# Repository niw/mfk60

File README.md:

mfk60
=====

60% ANSI Layout Split Keyboard. mfk60 is My First Keyboard, 60%.

- A split keyboard that has 60% ANSI Layout.
- Swappable Gateron Low-Profile MX keycap compatible switches.
- Thin design as MacBook Pro.
- USB-C interface.
- Fully customizable with [QMK firmware](https://qmk.fm/) and
  [VIA](https://www.caniusevia.com/) configuration.

Overview
--------

mfk60 is built with 4 layered boards, the top plate, middle plate, primary
PCB where the entire circuit exists, and bottom plate.

Each board is designed in separated KiCad project due to limitation of
KiCad which project can have only one board design.
Each layer board design contains both left and right designs.

- `sym-lib-table`, `fp-lib-table` are shared for additional symbol and
  footprint for all PCBs.
- `Library` contains additional symbols and footprints to KiCad.
- `mfk60.kicad_*` is the primary PCB of the keyboard.
- `mfk60_*_plate.kicad_*` are the each board layered with
  the primary PCB.
- `bin` contains tooling scripts.
- `mfk60_keyboard-layout.json` is key layout file for
  [Keyboard Layout Editor](http://www.keyboard-layout-editor.com/).

Photos
------

Build
-----

Since mfk60 is built with multiple KiCad projects, there are tooling
scripts to make the process easier.

### Overview

- `mfk60_keyboard-layout.json` to set the key layout.
- `make apply_layout` to apply the key layout to the primary PCB.
- `bin/prepare_plate_board.py` to sync the primary PCB and
  other layered board.
- `make panelize` to produce panelized boards that has frame and
  mouse bites.
- Produce Gerber files and BOM manually from KiCad projects for each board.

### Prerequisite

The board and tooling scripts are implemented by using
[KiCad](https://www.kicad.org/) 7.0.10 on macOS.

Please use KiCad 7.0.10 (or later, which is not tested.)

It should work on the other platform, however, you may need to use
`KICAD_PYTHON_PATH` to set where KiCad `python` exists
if it's not macOS or KiCad is installed on the different path
as like following.

```bash
env KICAD_PYTHON_PATH=/path/to/kicad/python bin/python.sh bin/update_plate_board.py
```

Each board is using symbols and footprints served from
[KiKit](https://github.com/yaqwsx/KiKit), which is referenced from
`.venv` library installation.
Thus, to open these PCB files, first need to install KiKit library.
To install KiKit, simply run `bin/kikit.sh`.

### Set key layout

Edit key layout on [Keyboard Layout Editor](http://www.keyboard-layout-editor.com/),
export the layout to `mfk60_keyboard-layout.json` then
use `apply_layout` goal to sync `mfk60_keyboard-layout.json`
to the primary PCB.

```bash
make apply_layout
```

Of course, it will invalidate existing PCB design, thus changing key
layout causes A LOT of work downstream.

### Sync layered boards

To sync Edge Cut and footprint positioning between the primary PCB and
the layered boards, use `bin/update_plate_board.py` with `bin/python.sh`.

```bash
bin/python.sh bin/update_plate_board.py
```

### Add frame and panelize

To produce final panelized projects with frame, use `panelize` make goal.

```bash
make panelize
```

This goal produces `mfk60*_panelized.kicad_*` files.
It adds frame, mouse bites and moves `JLCJLCJLCJLC` text onto the frame,
where is replaced with order number by [JLCPCB](https://jlcpcb.com/).

Panelized projects are final data that can be used to produce production
Gerber data. Recommend to use
[Fabrication Toolkit](https://github.com/bennymeg/JLC-Plugin-for-KiCad)
for JLCPCB but not limited ot it.

KiKit
-----

Due to multiple reasons as described below, this project is using
[forked version of KiKit](https://github.com/niw/KiKit/tree/v1.4.0_with_workaround).
`bin/kikit.sh` is automatically installs forked version of it in `.venv`,
therefore it's opaque to you.

### KiCad and Python Bindings

As of day this document is written, KiCad 7.0.10 and prior version has
a not well-known "behavior" (or simply say, a bug) in its Python binding
generated by [Swig](https://www.swig.org/).

Due to this issue, released KiKit will not work properly and may crash.
The forked version of it contains a workaround for this behavior.

### Multiple Polygons

Each layered board has both left and right ones, therefore each outline
is represented as multiple polygons.
However, original KiKit is not considering such multi polygon design and
failed to extract interior polygons which causes an error while
panelizing such data.

Firmware
--------

Use [forked QMK branch](https://github.com/niw/qmk_firmware/tree/mfk)
where contains the keyboard configuration.

```bash
qmk compile -kb niw/mfk60 -km default
```

It also works with VIA. Use `via` keymap and load
[`via.json`](https://github.com/niw/qmk_firmware/blob/mfk/keyboards/niw/mfk60/via.json)
for a draft definition in design tab enabled in settings.

```bash
qmk compile -kb niw/mfk60 -km via
```

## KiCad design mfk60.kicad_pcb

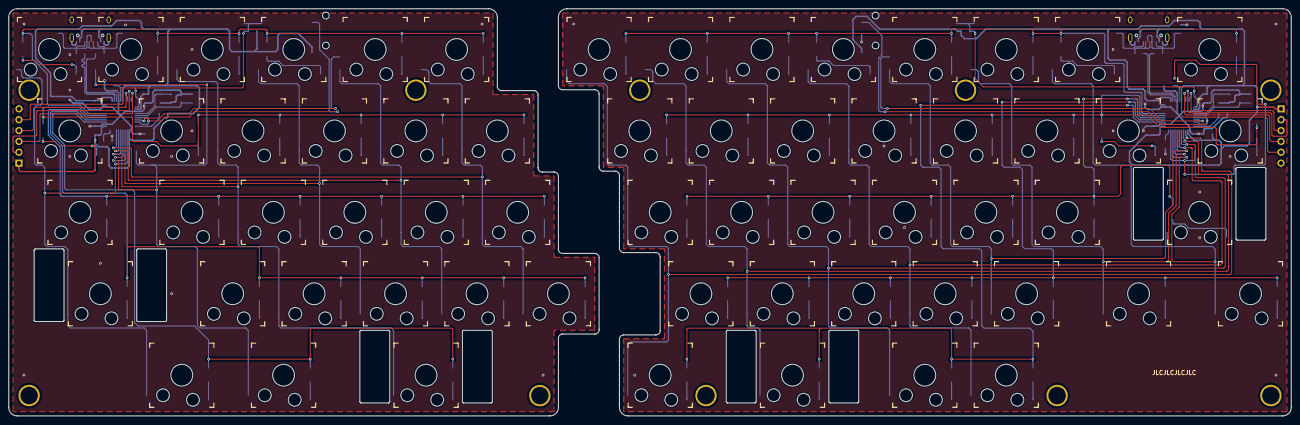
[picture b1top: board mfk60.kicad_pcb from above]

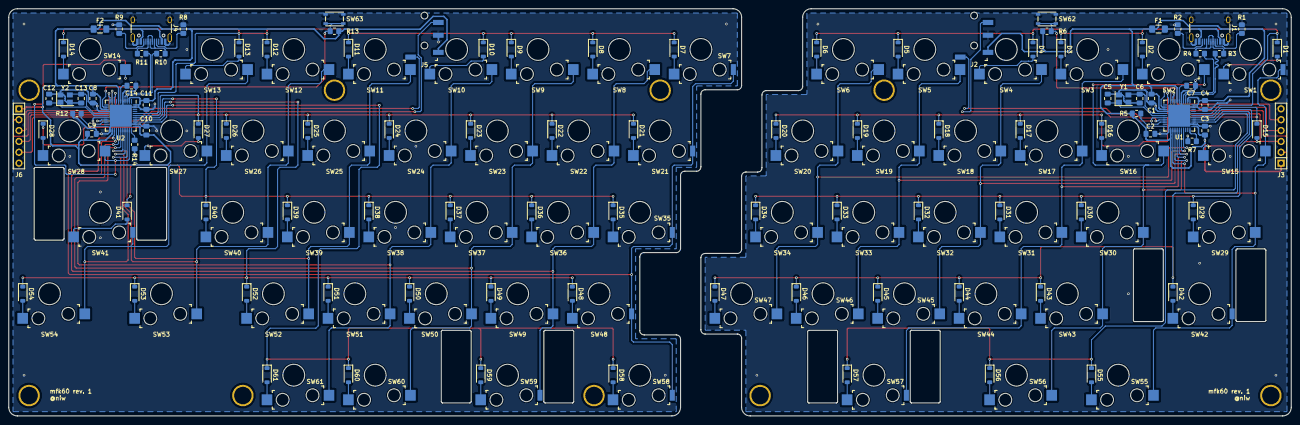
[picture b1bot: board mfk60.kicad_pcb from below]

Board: 2 copper layers, 300.0 x 95.2 mm, 181 parts (113 on the bottom side), 125 nets.

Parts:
C1, C2, C3, C8, C9, C10: 100n; C_0805_2012Metric_Pad1.18x1.45mm_HandSolder
C4, C11: 10u; C_0805_2012Metric_Pad1.18x1.45mm_HandSolder
C5, C6, C12, C13: 22p; C_0805_2012Metric_Pad1.18x1.45mm_HandSolder
C7, C14: 1u; C_0805_2012Metric_Pad1.18x1.45mm_HandSolder
D1, D2, D3, D4, D5, D6, D7, D8, D9, D10, D11, D12, D13, D14, D15, D16, D17, D18, D19, D20, D21, D22, D23, D24, D25, D26, D27, D28, D29, D30, D31, D32, D33, D34, D35, D36, D37, D38, D39, D40, D41, D42, D43, D44, D45, D46, D47, D48, D49, D50, D51, D52, D53, D54, D55, D56, D57, D58, D59, D60, D61: D; D_SOD-123
F1, F2: 500m; Fuse_1206_3216Metric_Pad1.42x1.75mm_HandSolder
H1, H2, H3, H4, H5, H6, H7, H8, H9, H10: MountingHole; MountingHole_4mm_Spacer
J1, J4: USB_C_Receptacle_USB2.0; USB_C_Receptacle_HRO_TYPE-C-31-M-12
J2, J5: TRRS Jack; TRRS_Jack_3.5mm_PJ320D
J3, J6: ISP; Debug_Pin_1x6_P2.54mm
R1, R2, R8, R9: 5.1k; R_0805_2012Metric_Pad1.20x1.40mm_HandSolder
R3, R4, R10, R11: 22; R_0805_2012Metric_Pad1.20x1.40mm_HandSolder
R5, R6, R7, R12, R13, R14: 10k; R_0805_2012Metric_Pad1.20x1.40mm_HandSolder
SW1, SW7, SW21, SW35, SW48, SW58: KS-33; Gateron_Low_Profile_Socket_Edge
SW2, SW3, SW4, SW5, SW6, SW8, SW9, SW10, SW11, SW12, SW13, SW14, SW15, SW16, SW17, SW18, SW19, SW20, SW22, SW23, SW24, SW25, SW26, SW27, SW28, SW29, SW30, SW31, SW32, SW33, SW34, SW36, SW37, SW38, SW39, SW40, SW43, SW44, SW45, SW46, SW47, SW49, SW50, SW51, SW52, SW53, SW54, SW55, SW56, SW60, SW61: KS-33; Gateron_Low_Profile_Socket
SW41, SW42, SW57, SW59: KS-33; Gateron_Low_Profile_Socket_Stabilizer_2U
SW62, SW63: RST; SW_Push_Alps_Alpine_SKRPACE010
T1, T2, T3, T4, T5, T6, T7: Tab
U1, U2: ATmega32U4-M; QFN-44-1EP_7x7mm_P0.5mm_EP5.2x5.2mm
Y1, Y2: 16M; Crystal_SMD_3225-4Pin_3.2x2.5mm

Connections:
+5V: C1.2, C2.2, C3.2, C4.2, F1.2, J2.4 (Tip), J3.1, R5.2, R6.2, U1.2 (UVCC), U1.7 (VBUS), U1.14 (VCC), U1.24 (AVCC), U1.34 (VCC), U1.44 (AVCC)
/Left/USB_CC1: J1.A5 (CC1), R1.1
/Left/USB_CC2: J1.B5 (CC2), R2.1
/Left/USB_VBUS: F1.1, J1.A4 (VBUS), J1.A9 (VBUS), J1.B4 (VBUS), J1.B9 (VBUS)
/Righ/R_USB_CC1: J4.A5 (CC1), R8.1
/Righ/R_USB_CC2: J4.B5 (CC2), R9.1
/Righ/R_USB_VBUS: F2.1, J4.A4 (VBUS), J4.A9 (VBUS), J4.B4 (VBUS), J4.B9 (VBUS)
COL1: SW1.1, SW15.1, SW29.1, SW42.1, SW55.1, U1.25 (PD4)
COL2: SW2.1, SW16.1, SW30.1, SW43.1, SW56.1, U1.26 (PD6)
COL3: SW3.1, SW17.1, SW31.1, SW44.1, SW57.1, U1.27 (PD7)
COL4: SW4.1, SW18.1, SW32.1, SW45.1, U1.28 (PB4)
COL5: SW5.1, SW19.1, SW33.1, SW46.1, U1.29 (PB5)
COL6: SW6.1, SW20.1, SW34.1, SW47.1, U1.30 (PB6)
COL7: SW7.1, SW21.1, SW35.1, SW48.1, SW58.1, U2.25 (PD4)
COL8: SW8.1, SW22.1, SW36.1, SW49.1, SW59.1, U2.26 (PD6)
COL9: SW9.1, SW23.1, SW37.1, SW50.1, SW60.1, U2.27 (PD7)
COL10: SW10.1, SW24.1, SW38.1, SW51.1, SW61.1, U2.28 (PB4)
COL11: SW11.1, SW25.1, SW39.1, SW52.1, U2.29 (PB5)
COL12: SW12.1, SW26.1, SW40.1, SW53.1, U2.30 (PB6)
COL13: SW13.1, SW27.1, SW41.1, SW54.1, U2.31 (PC6)
COL14: SW14.1, SW28.1, U2.32 (PC7)
GND: C1.1, C2.1, C3.1, C4.1, C5.2, C6.2, C7.1, J1.A1 (GND), J1.A12 (GND), J1.B1 (GND), J1.B12 (GND), J1.S1 (SHIELD), J2.3 (Ring_1), J3.6, R1.2, R2.2, R7.1, SW62.2, U1.5 (UGND), U1.15 (GND), U1.23 (GND), U1.35 (GND), U1.43 (GND), U1.45 (GND), Y1.2, Y1.4
MISO: J3.3, U1.11 (PB3)
MOSI: J3.2, U1.10 (PB2)
unnamed: D1.2 (A), SW1.2
unnamed: D2.2 (A), SW2.2
unnamed: D3.2 (A), SW3.2
unnamed: D4.2 (A), SW4.2
unnamed: D5.2 (A), SW5.2
unnamed: D6.2 (A), SW6.2
unnamed: D7.2 (A), SW7.2
unnamed: D8.2 (A), SW8.2
unnamed: D9.2 (A), SW9.2
unnamed: D10.2 (A), SW10.2
unnamed: D11.2 (A), SW11.2
unnamed: D12.2 (A), SW12.2
unnamed: D13.2 (A), SW13.2
unnamed: D14.2 (A), SW14.2
unnamed: D15.2 (A), SW15.2
unnamed: D16.2 (A), SW16.2
unnamed: D17.2 (A), SW17.2
unnamed: D18.2 (A), SW18.2
unnamed: D19.2 (A), SW19.2
unnamed: D20.2 (A), SW20.2
unnamed: D21.2 (A), SW21.2
unnamed: D22.2 (A), SW22.2
unnamed: D23.2 (A), SW23.2
unnamed: D24.2 (A), SW24.2
unnamed: D25.2 (A), SW25.2
unnamed: D26.2 (A), SW26.2
unnamed: D27.2 (A), SW27.2
unnamed: D28.2 (A), SW28.2
unnamed: D29.2 (A), SW29.2
unnamed: D30.2 (A), SW30.2
unnamed: D31.2 (A), SW31.2
unnamed: D32.2 (A), SW32.2
unnamed: D33.2 (A), SW33.2
unnamed: D34.2 (A), SW34.2
unnamed: D35.2 (A), SW35.2
unnamed: D36.2 (A), SW36.2
unnamed: D37.2 (A), SW37.2
unnamed: D38.2 (A), SW38.2
unnamed: D39.2 (A), SW39.2
unnamed: D40.2 (A), SW40.2
unnamed: D41.2 (A), SW41.2
unnamed: D42.2 (A), SW42.2
unnamed: D43.2 (A), SW43.2
unnamed: D44.2 (A), SW44.2
unnamed: D45.2 (A), SW45.2
unnamed: D46.2 (A), SW46.2
unnamed: D47.2 (A), SW47.2
unnamed: D48.2 (A), SW48.2
unnamed: D49.2 (A), SW49.2
unnamed: D50.2 (A), SW50.2
unnamed: D51.2 (A), SW51.2
unnamed: D52.2 (A), SW52.2
unnamed: D53.2 (A), SW53.2
unnamed: D54.2 (A), SW54.2
unnamed: D55.2 (A), SW55.2
unnamed: D56.2 (A), SW56.2
unnamed: D57.2 (A), SW57.2
unnamed: D58.2 (A), SW58.2
unnamed: D59.2 (A), SW59.2
unnamed: D60.2 (A), SW60.2
unnamed: D61.2 (A), SW61.2
unnamed: J1.A6 (D+), J1.B6 (D+), R4.1
unnamed: J1.A7 (D-), J1.B7 (D-), R3.1
unnamed: J4.A6 (D+), J4.B6 (D+), R11.1
unnamed: J4.A7 (D-), J4.B7 (D-), R10.1
unnamed: C7.2, U1.6 (UCAP)
unnamed: R7.2, U1.33 (~HWB/PE2)
unnamed: C14.2, U2.6 (UCAP)
unnamed: R14.2, U2.33 (~HWB/PE2)
RESET: J3.5, R6.1, SW62.1, U1.13 (~RESET)
ROW1: D1.1 (K), D2.1 (K), D3.1 (K), D4.1 (K), D5.1 (K), D6.1 (K), U1.40 (PF1)
ROW2: D15.1 (K), D16.1 (K), D17.1 (K), D18.1 (K), D19.1 (K), D20.1 (K), U1.39 (PF4)
ROW3: D29.1 (K), D30.1 (K), D31.1 (K), D32.1 (K), D33.1 (K), D34.1 (K), U1.38 (PF5)
ROW4: D42.1 (K), D43.1 (K), D44.1 (K), D45.1 (K), D46.1 (K), D47.1 (K), U1.37 (PF6)
ROW5: D55.1 (K), D56.1 (K), D57.1 (K), U1.36 (PF7)
R_+5V: C8.2, C9.2, C10.2, C11.2, F2.2, J5.4 (Tip), J6.1, R13.2, U2.2 (UVCC), U2.7 (VBUS), U2.14 (VCC), U2.24 (AVCC), U2.34 (VCC), U2.44 (AVCC)
R_GND: C8.1, C9.1, C10.1, C11.1, C12.2, C13.2, C14.1, J4.A1 (GND), J4.A12 (GND), J4.B1 (GND), J4.B12 (GND), J4.S1 (SHIELD), J5.3 (Ring_1), J6.6, R8.2, R9.2, R12.1, R14.1, SW63.2, U2.5 (UGND), U2.15 (GND), U2.23 (GND), U2.35 (GND), U2.43 (GND), U2.45 (GND), Y2.2, Y2.4
R_MISO: J6.3, U2.11 (PB3)
R_MOSI: J6.2, U2.10 (PB2)
R_RESET: J6.5, R13.1, SW63.1, U2.13 (~RESET)
R_ROW1: D7.1 (K), D8.1 (K), D9.1 (K), D10.1 (K), D11.1 (K), D12.1 (K), D13.1 (K), D14.1 (K), U2.40 (PF1)
R_ROW2: D21.1 (K), D22.1 (K), D23.1 (K), D24.1 (K), D25.1 (K), D26.1 (K), D27.1 (K), D28.1 (K), U2.39 (PF4)
R_ROW3: D35.1 (K), D36.1 (K), D37.1 (K), D38.1 (K), D39.1 (K), D40.1 (K), D41.1 (K), U2.38 (PF5)
R_ROW4: D48.1 (K), D49.1 (K), D50.1 (K), D51.1 (K), D52.1 (K), D53.1 (K), D54.1 (K), U2.37 (PF6)
R_ROW5: D58.1 (K), D59.1 (K), D60.1 (K), D61.1 (K), U2.36 (PF7)
R_SCLK: J6.4, U2.9 (PB1)
R_SCL_SERIAL: J5.2 (Ring_2), U2.18 (PD0), U2.20 (PD2)
R_SDA: J5.5 (Sleeve), U2.19 (PD1)
R_SPLIT_HAND: R12.2, U2.22 (PD5)
R_USB_D+: R11.2, U2.4 (D+)
R_USB_D-: R10.2, U2.3 (D-)
R_XTAL1: C12.1, U2.17 (XTAL1), Y2.1
R_XTAL2: C13.1, U2.16 (XTAL2), Y2.3
SCLK: J3.4, U1.9 (PB1)
SCL_SERIAL: J2.2 (Ring_2), U1.18 (PD0), U1.20 (PD2)
SDA: J2.5 (Sleeve), U1.19 (PD1)
SPLIT_HAND: R5.1, U1.22 (PD5)
USB_D+: R4.2, U1.4 (D+)
USB_D-: R3.2, U1.3 (D-)
XTAL1: C5.1, U1.17 (XTAL1), Y1.1
XTAL2: C6.1, U1.16 (XTAL2), Y1.3

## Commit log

2023-12-02 Initial.
2023-12-03 Add kbplacer wrapper script.
2023-12-27 Add kikit wrapper script.
2024-01-12 Add a script to create plate boards.
2024-01-12 Initial complete work of mfk60.
2024-01-12 Adjust JLC text position and add it to script.
2024-01-13 Add pull-up resistor on left side.
2024-01-13 Cleanup script.
2024-01-13 FIX: key and diode value
2024-01-13 Adjust differential pairs
2024-01-13 Minor alignment fix.
2024-01-13 Update comments.
2024-01-13 Add missing npth for USB-C socket.
2024-01-13 Change script options.
2024-01-13 Add missing cut for USB-C socket.
2024-01-25 Manage object lifecycle properly, remove net from pads.
2024-01-25 Use patched version of KiKit.
    Use updated branch
2024-01-25 Multiple changes to produce production file
    - Set missing board only flag.
    - Set exclude from position files flags as well.
    - Update JCL text position for plates.
    - Fix origin.
    - Minor updates.
2024-01-25 Organize bin directory and scripts.
2024-01-25 Update layout file.
2024-01-25 Add layout for VIA keymap.
2024-01-25 Update KiKit config.
2024-01-25 Add README and LICENSE files.
2024-01-25 Update Bash scripts.
    - `KICAD_PYTHON_PATH` to change KiCad `python` path.
    - Set protective Bash options.
    - Use `readonly`.
2024-01-25 Update README.
2024-01-27 Add QMK formware and VIA usage.
2024-01-29 Update and add photos.
